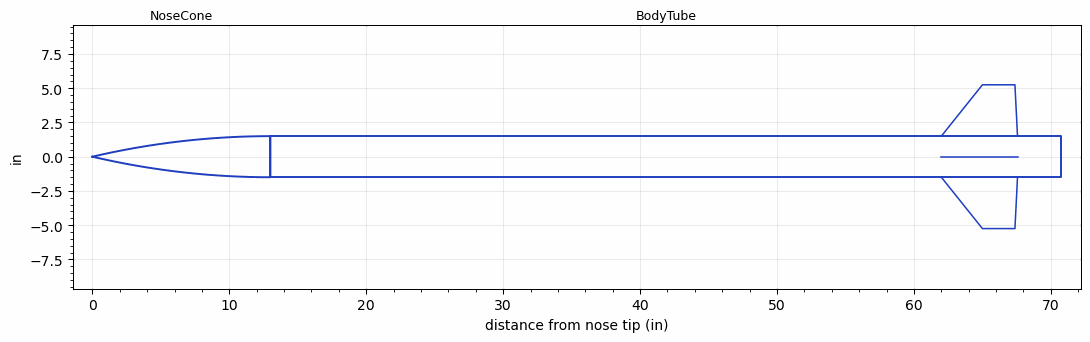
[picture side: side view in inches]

<RASAeroDocument>
 <FileVersion>2</FileVersion>
 <RocketDesign>
  <NoseCone>
   <Length>13</Length>
   <Diameter>3</Diameter>
   <Shape>Tangent Ogive</Shape>
   <Location>0</Location>
  </NoseCone>
  <BodyTube>
   <Length>57.75</Length>
   <Diameter>3</Diameter>
   <LaunchShoeArea>0.075</LaunchShoeArea>
   <Location>13</Location>
   <Fin>
    <Count>4</Count>
    <Chord>5.5625</Chord>
    <Span>3.75</Span>
    <SweepDistance>3</SweepDistance>
    <TipChord>2.375</TipChord>
    <Thickness>0.093</Thickness>
    <Location>8.75</Location>
    <AirfoilSection>Rounded</AirfoilSection>
    <FX1>1.5</FX1>
    <FX3>1.25</FX3>
   </Fin>
  </BodyTube>
  <Surface>Smooth (Zero Roughness)</Surface>
  <ModifiedBarrowman>False</ModifiedBarrowman>
  <Turbulence>False</Turbulence>
  <UseBooster1>False</UseBooster1>
  <UseBooster2>False</UseBooster2>
  <Comments>LDRS-26
Jean Dry Lake

Barometric Altimeter
Altitude = 3913 ft

RASAero II Prediction = 4205 ft
Error = 7.46%
</Comments>
 </RocketDesign>
 <LaunchSite>
  <Altitude>2750</Altitude>
  <Pressure>0</Pressure>
  <RodAngle>0</RodAngle>
  <RodLength>10</RodLength>
  <Temperature>100</Temperature>
  <WindSpeed>0</WindSpeed>
 </LaunchSite>
 <Recovery>
  <Altitude1>1000</Altitude1>
  <Altitude2>1000</Altitude2>
  <DeviceType1>None</DeviceType1>
  <DeviceType2>None</DeviceType2>
  <Event1>False</Event1>
  <Event2>False</Event2>
  <Size1>1</Size1>
  <Size2>1</Size2>
  <EventType1>None</EventType1>
  <EventType2>None</EventType2>
  <CD1>1.33</CD1>
  <CD2>1.33</CD2>
 </Recovery>
 <SimulationList>
  <Simulation>
   <SustainerEngine>I284W  (AT)</SustainerEngine>
   <SustainerLaunchWt>6.16</SustainerLaunchWt>
   <SustainerCG>50.5</SustainerCG>
   <SustainerIgnitionDelay>0</SustainerIgnitionDelay>
   <Booster1SeparationDelay>0</Booster1SeparationDelay>
   <Booster1IgnitionDelay>0</Booster1IgnitionDelay>
   <IncludeBooster1>False</IncludeBooster1>
   <Booster2Delay>0</Booster2Delay>
   <IncludeBooster2>False</IncludeBooster2>
   <TimetoApogee>15.29025</TimetoApogee>
   <MaxAltitude>4205.14</MaxAltitude>
   <MaxVelocity>638.2443</MaxVelocity>
  </Simulation>
 </SimulationList>
</RASAeroDocument>
